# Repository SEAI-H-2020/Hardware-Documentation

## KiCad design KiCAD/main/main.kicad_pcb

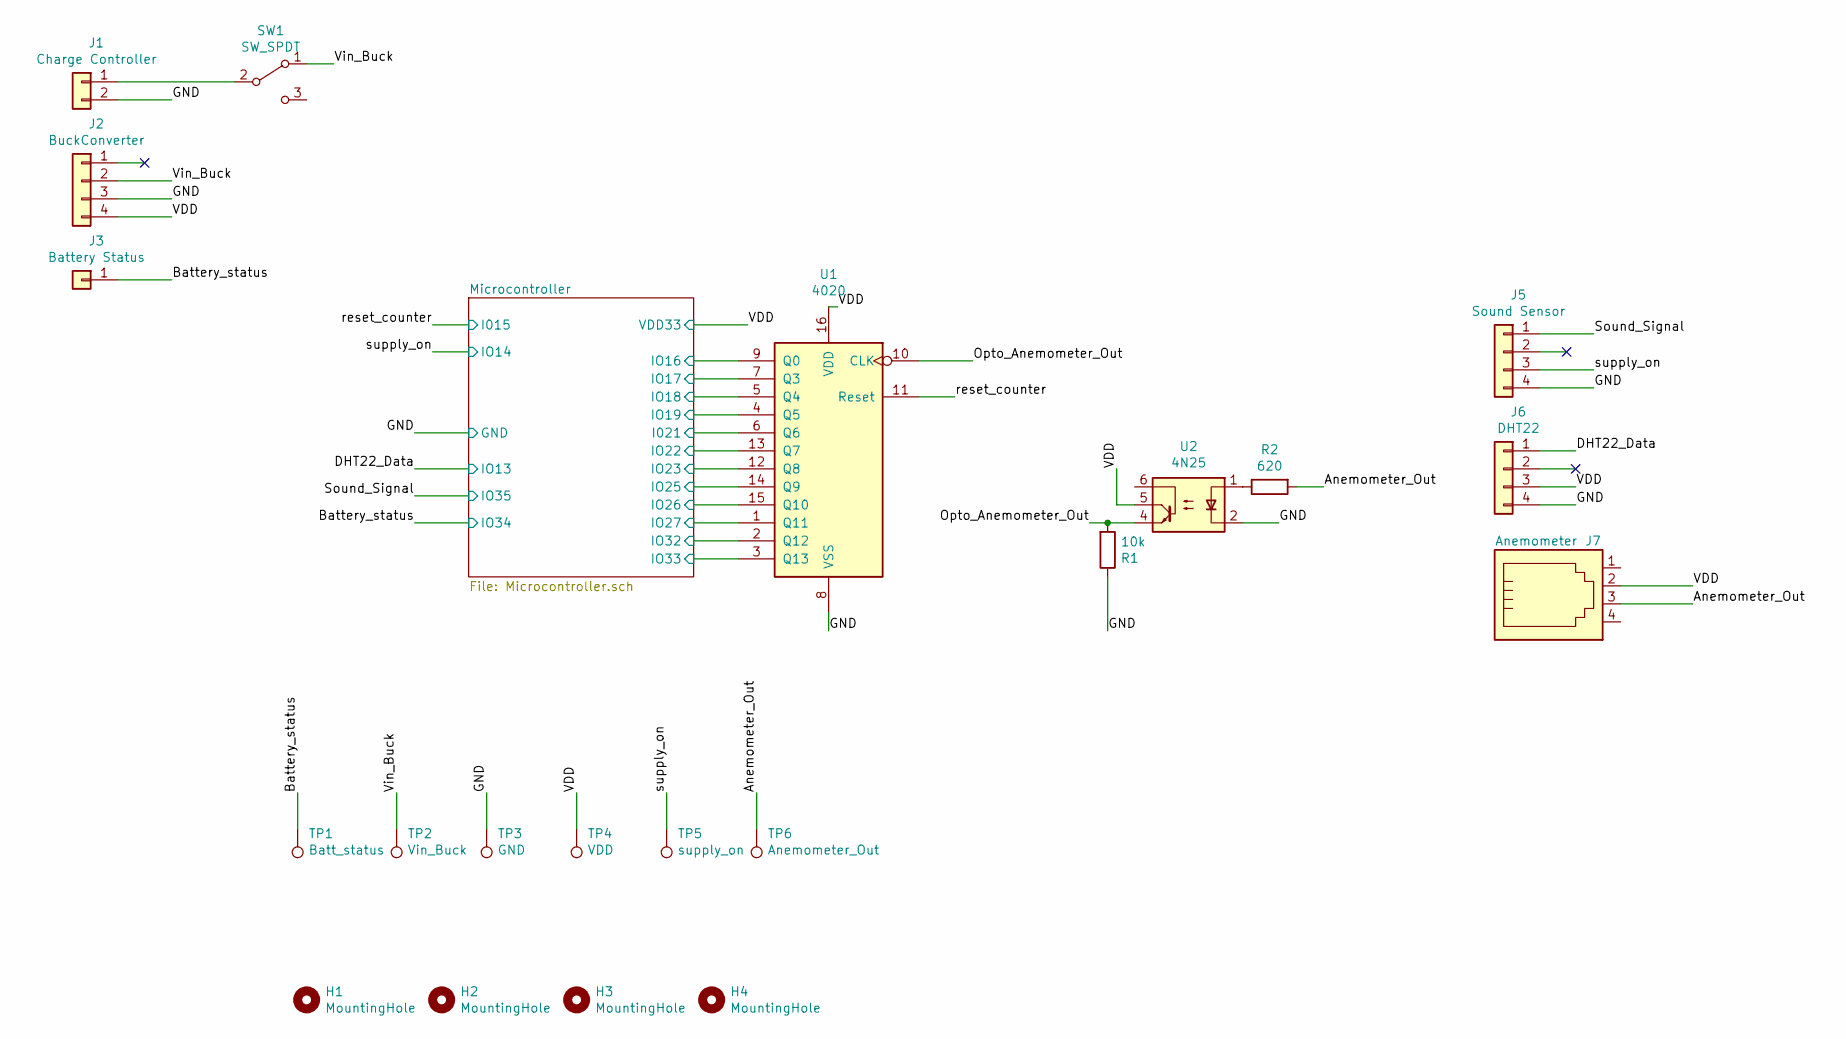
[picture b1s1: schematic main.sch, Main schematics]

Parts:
H1, H2, H3, H4: MountingHole; MountingHole_3.2mm_M3_Pad
J1: Charge Controller; JST_PH_B2B-PH-K_1x02_P2.00mm_Vertical
J2: BuckConverter; PinSocket_1x04_P2.54mm_Vertical
J3: Battery Status; PinHeader_1x01_P2.54mm_Vertical
J5: Sound Sensor; NS-Tech_Grove_1x04_P2mm_Vertical
J6: DHT22; NS-Tech_Grove_1x04_P2mm_Vertical
J7: Anemometer; RJ14_Connfly_DS1133-S4_Horizontal
R1: 10k; R_Axial_DIN0207_L6.3mm_D2.5mm_P10.16mm_Horizontal
R2: 620; R_Axial_DIN0207_L6.3mm_D2.5mm_P10.16mm_Horizontal
SW1: SW_SPDT; SW_CuK_JS202011AQN_DPDT_Angled
TP1: Batt_status; TestPoint_Pad_1.0x1.0mm
TP2: Vin_Buck; TestPoint_Pad_1.0x1.0mm
TP3: GND; TestPoint_Pad_1.0x1.0mm
TP4: VDD; TestPoint_Pad_1.0x1.0mm
TP5: supply_on; TestPoint_Pad_1.0x1.0mm
TP6: Anemometer_Out; TestPoint_Pad_1.0x1.0mm
U1: 4020; DIP-16_W7.62mm_LongPads
U2: 4N25; DIP-6_W7.62mm_LongPads

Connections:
+3V3: J2.4, J6.3, J7.2, TP4.1, U1.16 (VDD), U2.5; also elsewhere on the board
/Anemometer_Out: J7.3, R2.2, TP6.1
/Battery_status: J3.1, TP1.1; also elsewhere on the board
/DHT22_Data: J6.1; also elsewhere on the board
/Microcontroller/I021: U1.6 (Q6); also elsewhere on the board
/Microcontroller/IO16: U1.9 (Q0); also elsewhere on the board
/Microcontroller/IO17: U1.7 (Q3); also elsewhere on the board
/Microcontroller/IO18: U1.5 (Q4); also elsewhere on the board
/Microcontroller/IO19: U1.4 (Q5); also elsewhere on the board
/Microcontroller/IO22: U1.13 (Q7); also elsewhere on the board
/Microcontroller/IO23: U1.12 (Q8); also elsewhere on the board
/Microcontroller/IO25: U1.14 (Q9); also elsewhere on the board
/Microcontroller/IO26: U1.15 (Q10); also elsewhere on the board
/Microcontroller/IO27: U1.1 (Q11); also elsewhere on the board
/Microcontroller/IO32: U1.2 (Q12); also elsewhere on the board
/Microcontroller/IO33: U1.3 (Q13); also elsewhere on the board
/Opto_Anemometer_Out: R1.2, U1.10 (CLK), U2.4
/Sound_Signal: J5.1; also elsewhere on the board
/Vin_Buck: J2.2, SW1.1 (A), TP2.1
/reset_counter: U1.11 (Reset); also elsewhere on the board
/supply_on: J5.3, TP5.1; also elsewhere on the board
GND: J1.2, J2.3, J5.4, J6.4, R1.1, TP3.1, U1.8 (VSS), U2.2; also elsewhere on the board
unnamed: J1.1, SW1.2 (B)
unnamed: R2.1, U2.1

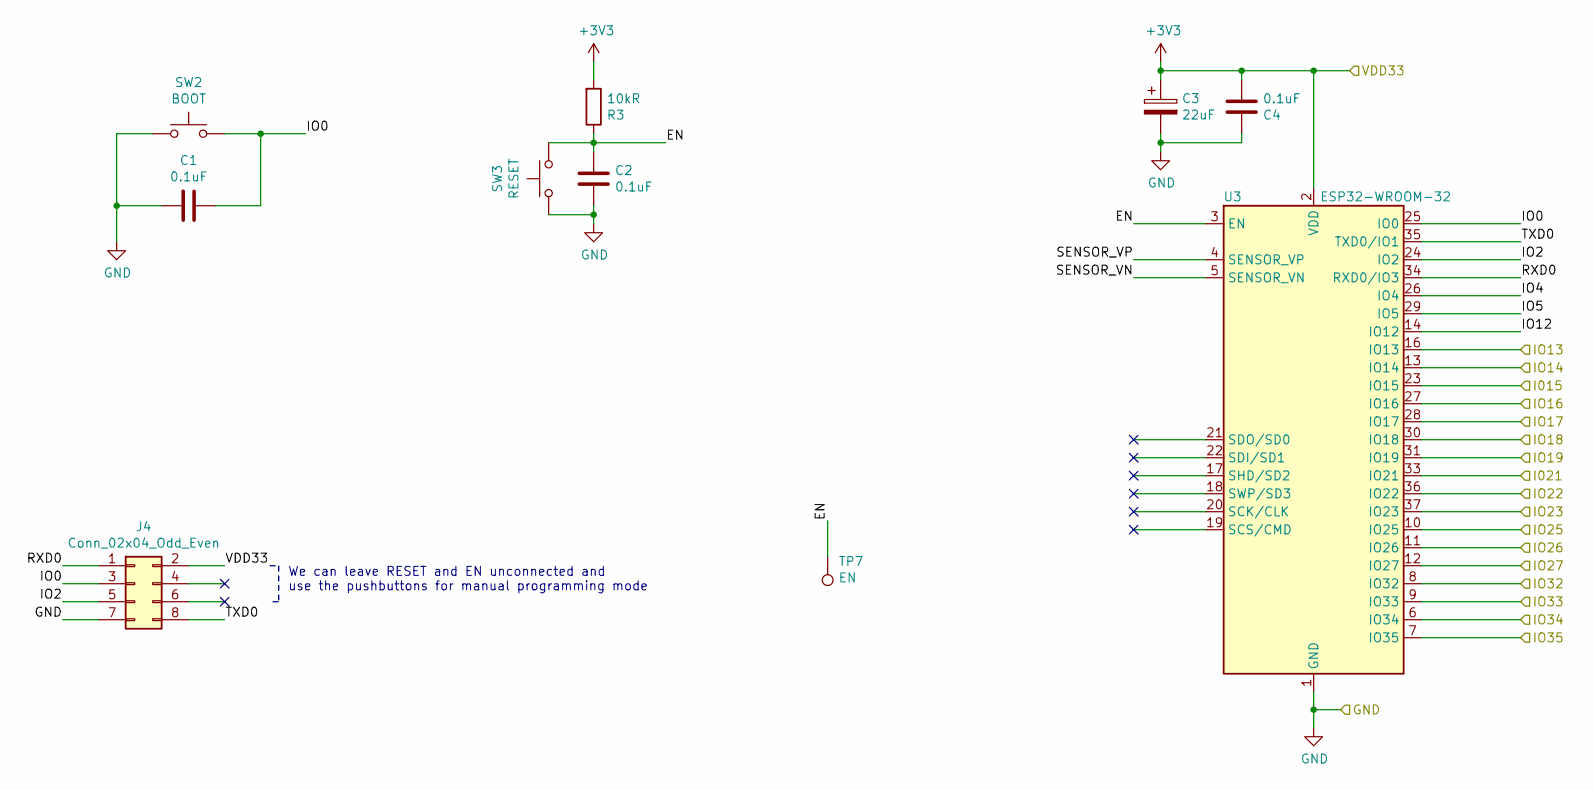
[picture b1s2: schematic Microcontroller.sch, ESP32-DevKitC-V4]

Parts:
C1, C4: 0.1uF; C_Disc_D4.3mm_W1.9mm_P5.00mm; Voltage 50V
C2: 0.1uF; C_Disc_D4.3mm_W1.9mm_P5.00mm; Voltage 50V; Tolerance 10%
C3: 22uF; CP_Radial_D6.3mm_P2.50mm; Voltage 10V
J4: Conn_02x04_Odd_Even; PinHeader_2x04_P2.54mm_Vertical
R3: 10kR; R_Axial_DIN0207_L6.3mm_D2.5mm_P10.16mm_Horizontal
SW2: BOOT; SW_PUSH_6mm
SW3: RESET; SW_PUSH_6mm
TP7: EN; TestPoint_Pad_1.0x1.0mm
U3: ESP32-WROOM-32

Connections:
+3V3: C3.1, C4.2, J4.2, R3.2, U3.2 (VDD); also elsewhere on the board
/Battery_status: U3.6 (IO34); also elsewhere on the board
/DHT22_Data: U3.16 (IO13); also elsewhere on the board
/Microcontroller/EN: C2.1, R3.1, SW3.2, TP7.1, U3.3 (EN)
/Microcontroller/I021: U3.33 (IO21); also elsewhere on the board
/Microcontroller/IO0: C1.2, J4.3, SW2.2, U3.25 (IO0)
/Microcontroller/IO2: J4.5, U3.24 (IO2)
/Microcontroller/IO4: U3.26 (IO4)
/Microcontroller/IO5: U3.29 (IO5)
/Microcontroller/IO12: U3.14 (IO12)
/Microcontroller/IO16: U3.27 (IO16); also elsewhere on the board
/Microcontroller/IO17: U3.28 (IO17); also elsewhere on the board
/Microcontroller/IO18: U3.30 (IO18); also elsewhere on the board
/Microcontroller/IO19: U3.31 (IO19); also elsewhere on the board
/Microcontroller/IO22: U3.36 (IO22); also elsewhere on the board
/Microcontroller/IO23: U3.37 (IO23); also elsewhere on the board
/Microcontroller/IO25: U3.10 (IO25); also elsewhere on the board
/Microcontroller/IO26: U3.11 (IO26); also elsewhere on the board
/Microcontroller/IO27: U3.12 (IO27); also elsewhere on the board
/Microcontroller/IO32: U3.8 (IO32); also elsewhere on the board
/Microcontroller/IO33: U3.9 (IO33); also elsewhere on the board
/Microcontroller/RXD0: J4.1, U3.34 (RXD0/IO3)
/Microcontroller/SENSOR_VN: U3.5 (SENSOR_VN)
/Microcontroller/SENSOR_VP: U3.4 (SENSOR_VP)
/Microcontroller/TXD0: J4.8, U3.35 (TXD0/IO1)
/Sound_Signal: U3.7 (IO35); also elsewhere on the board
/reset_counter: U3.23 (IO15); also elsewhere on the board
/supply_on: U3.13 (IO14); also elsewhere on the board
GND: C1.1, C2.2, C3.2, C4.1, J4.7, SW2.1, SW3.1, U3.1 (GND), U3.15 (GND), U3.38 (GND), U3.39 (GND); also elsewhere on the board

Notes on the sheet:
We can leave RESET and EN unconnected and use the pushbuttons for manual programming mode

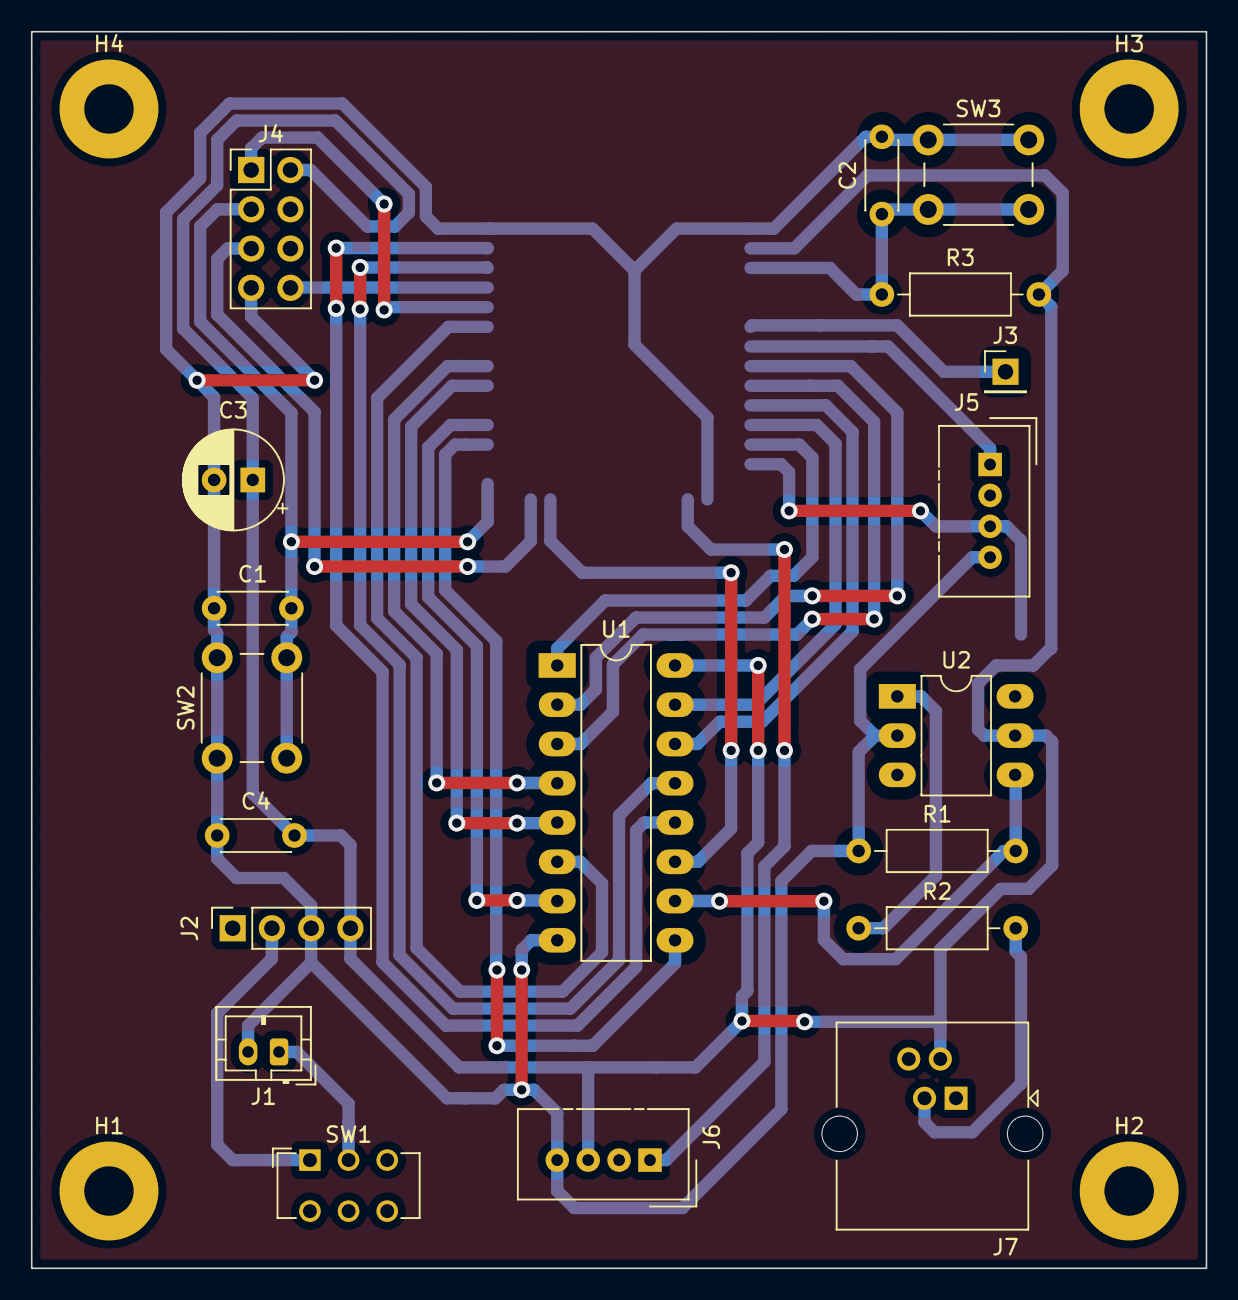
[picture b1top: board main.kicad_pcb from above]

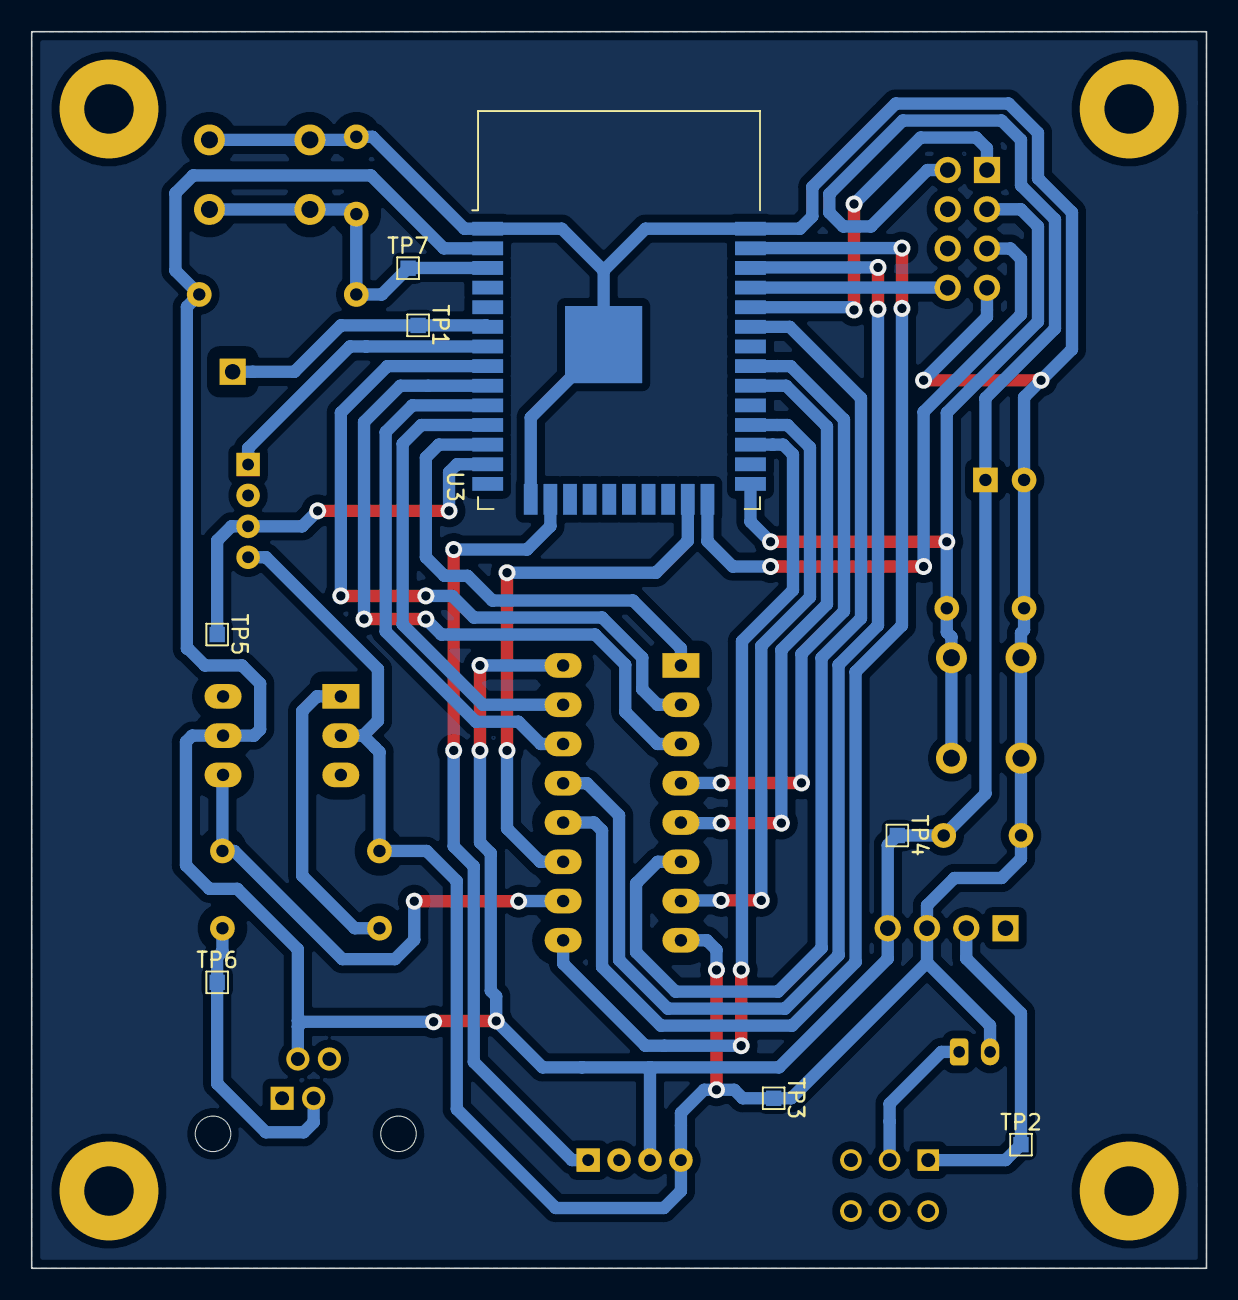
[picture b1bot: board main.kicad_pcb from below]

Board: 2 copper layers, 76.0 x 80.0 mm, 31 parts (8 on the bottom side), 29 nets.

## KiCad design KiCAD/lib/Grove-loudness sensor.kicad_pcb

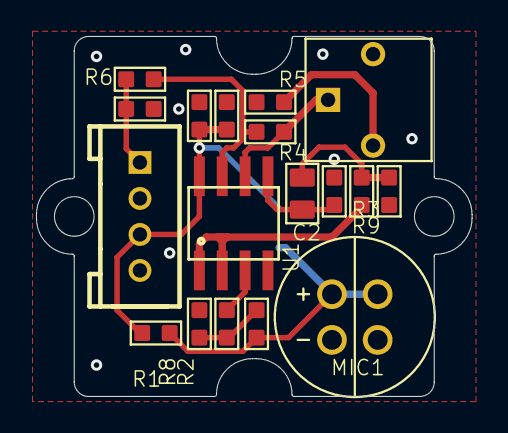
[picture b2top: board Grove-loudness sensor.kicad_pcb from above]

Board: 2 copper layers, 24.2 x 20.0 mm, 23 parts (0 on the bottom side), 12 nets.

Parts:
C1, C3, C5: 1uF; C0603
C2: 4.7uF; C0805
C4: 100nF; C0603
C6: 4.7pF; C0603
J2: TWIG_2.0; 2.0_1X4
MIC1, MIC2: microphone; 2P-D8.9MM
R1: 10k; R0603
R2, R8: 100k; R0603
R3: 16K; R0603
R4: 560k; R0603
R5: 1K; R0603
R6: 47K; R0603
R7: 1k; 3P-SQUA-7X6.8
R9: 10K; R0603
U1: LM2904DR; SO08
U4: SENSOR-MULPS4CX; 4P-SMD-2.95X3.76X1.1H
U$1: OSHW_FILLX150_NOTEXT
U$2: 1U-DIM-W_-DRILL
U$3: TWIGLOGO

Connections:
/MIC: C1.1, MIC1.1, MIC2.1, R1.1, U4.1
/SIG: C3.1, J2.1, R6.2
/VCC: C4.1, C5.2, J2.3, R1.2, U4.4
GND: C3.2, C4.2, C5.1, C6.1, J2.4, MIC1.2, MIC2.2, R3.1, R5.1, R8.1, U1.4, U4.2, U4.3
unnamed: C1.2, R2.1, R8.2
unnamed: C2.1, R3.2, U1.5
unnamed: C2.2, C6.2, R9.2
unnamed: R2.2, U1.3
unnamed: R4.1, R7.3, U1.6
unnamed: R4.2, R6.1, U1.7
unnamed: R5.2, R7.1
unnamed: R9.1, U1.1, U1.2

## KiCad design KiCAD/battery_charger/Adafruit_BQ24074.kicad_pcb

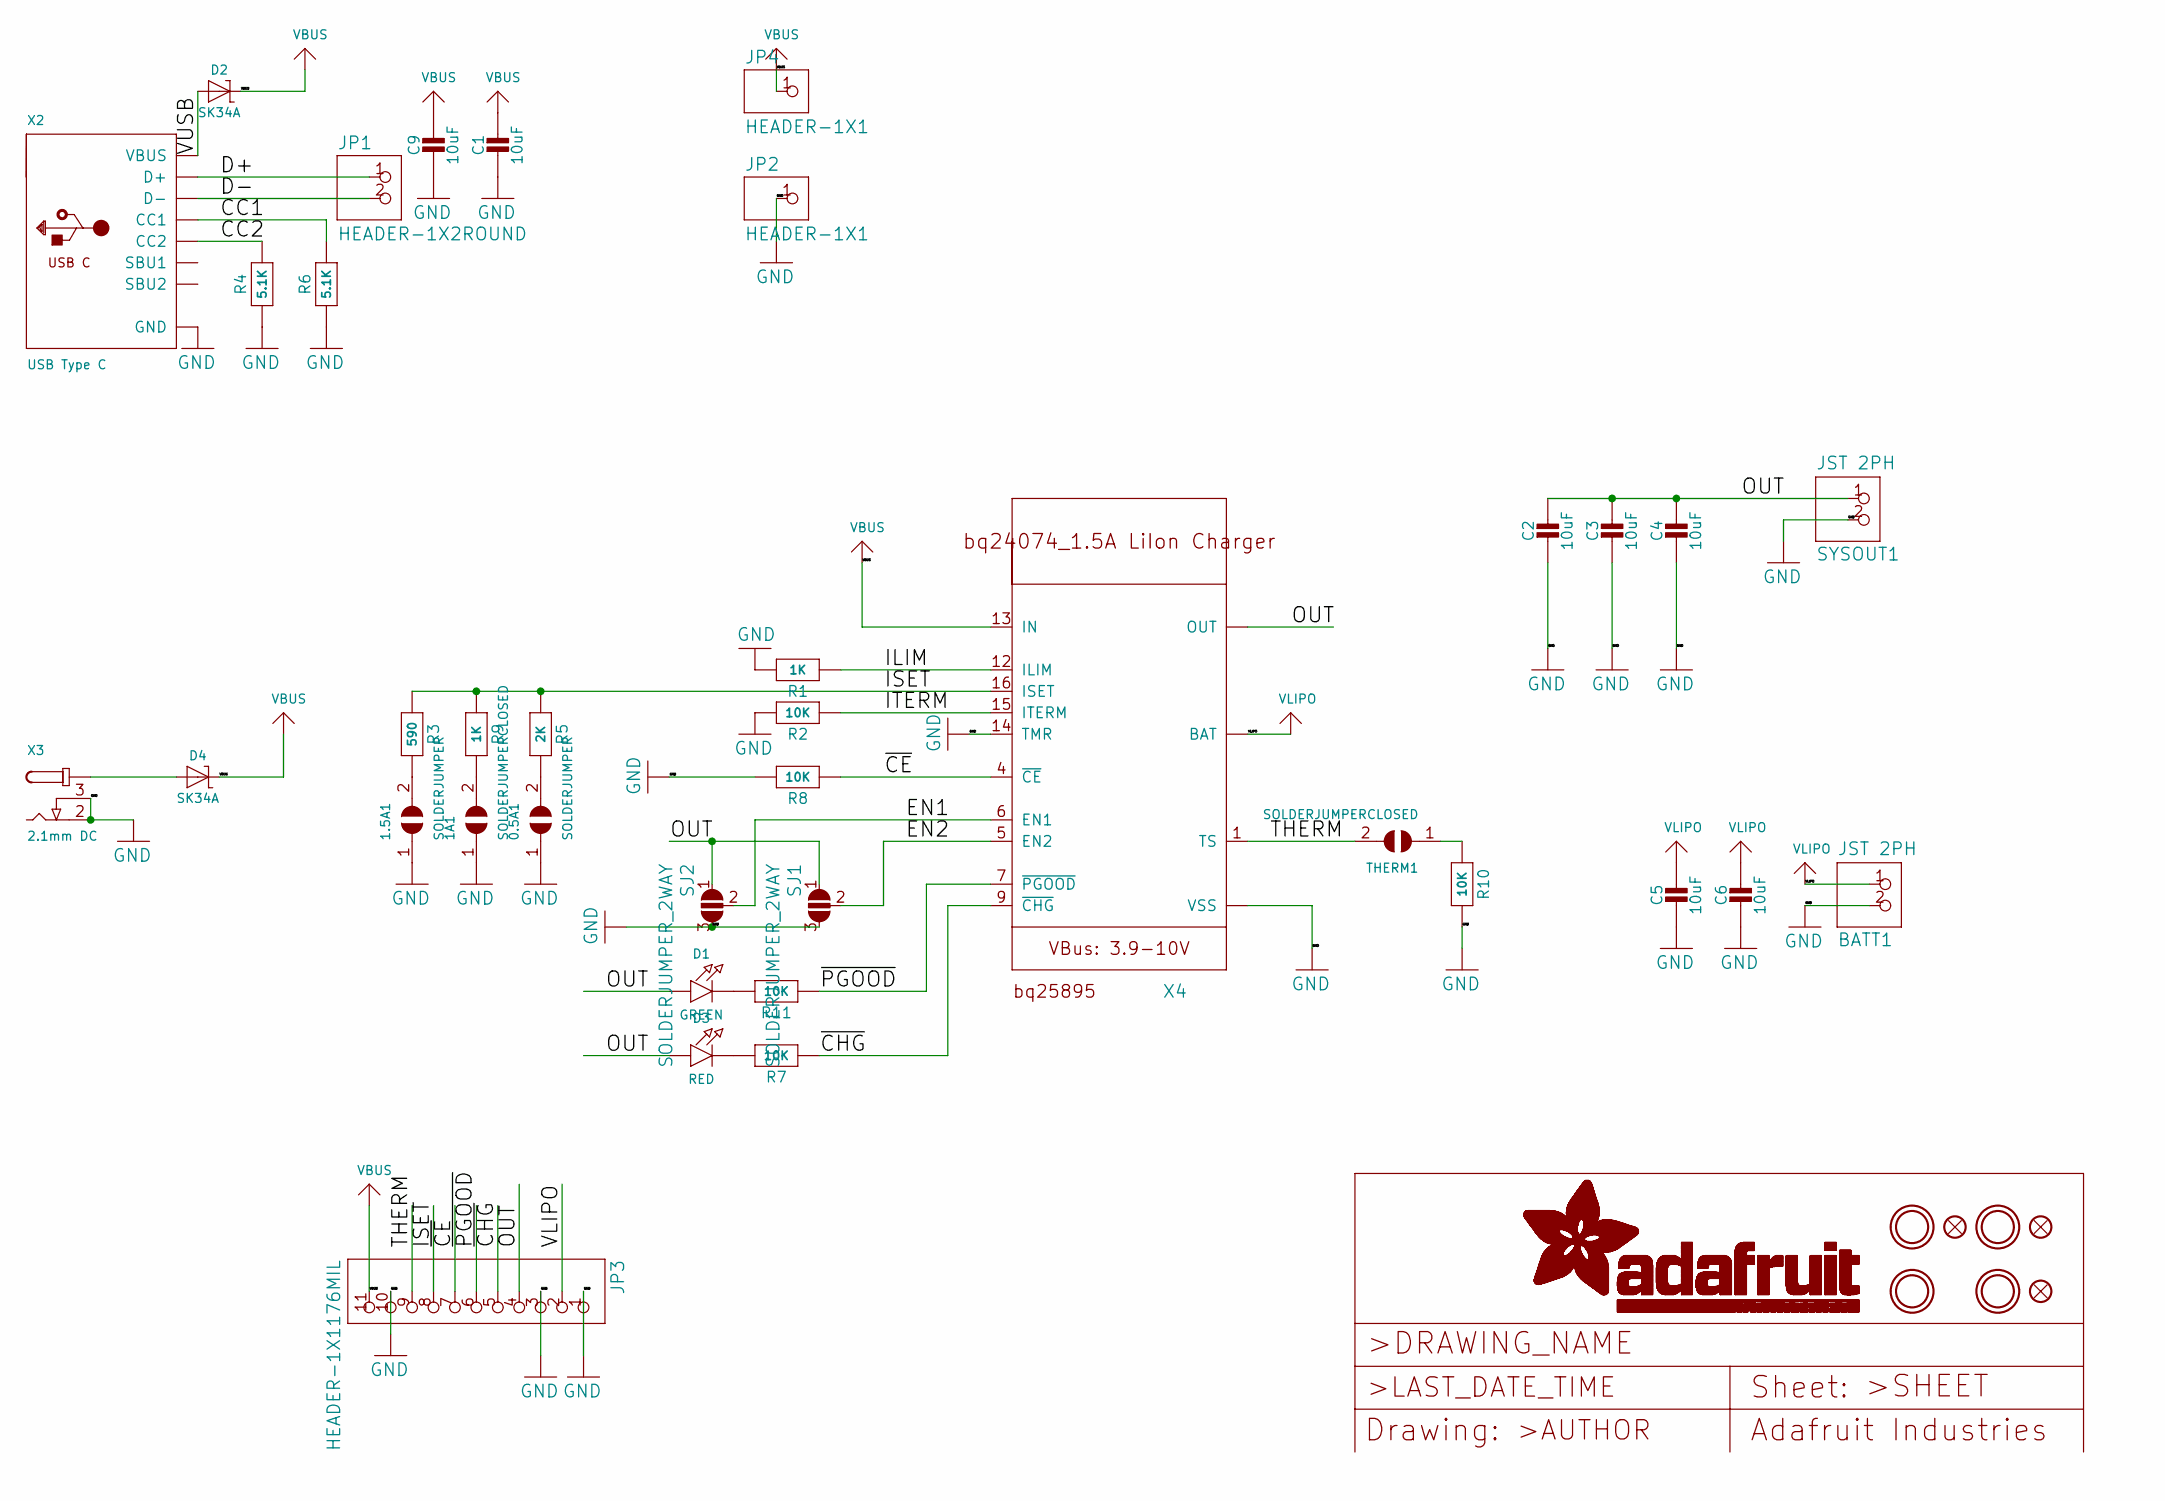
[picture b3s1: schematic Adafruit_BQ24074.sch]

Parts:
0.5A1, 1.5A1: SOLDERJUMPER; SOLDERJUMPER_ARROW_NOPASTE
1A1: SOLDERJUMPERCLOSED; SOLDERJUMPER_CLOSEDWIRE
BATT1: JST 2PH; JST-PH-2-SMT-RA
C1, C2, C3, C4, C5, C6, C9: 10uF; 0805-NO
D1: GREEN; CHIPLED_0603
D2, D4: SK34A; SMADIODE
D3: RED; CHIPLED_0603
FID1, FID2, FID3: FIDUCIAL_1MM
JP1: HEADER-1X2ROUND; 1X02_ROUND
JP2, JP4: HEADER-1X1; 1X01_OVAL
JP3: HEADER-1X1176MIL; 1X11_ROUND_76
R1, R9: 1K; 0603-NO
R2, R7, R8, R10, R11: 10K; 0603-NO
R3: 590; 0603-NO
R4, R6: 5.1K; 0603-NO
R5: 2K; 0603-NO
SJ1, SJ2: SOLDERJUMPER_2WAY; SOLDERJUMPER_2WAY_OPEN_NOPASTE
SYSOUT1: JST 2PH; JST-PH-2-SMT-RA
THERM1: SOLDERJUMPERCLOSED; SOLDERJUMPER_CLOSEDWIRE
U$3, U$4, U$11, U$12: MOUNTINGHOLE2.5; MOUNTINGHOLE_2.5_PLATED
X2: USB Type C; USB_C_CUSB31-CFM2AX-01-X
X3: 2.1mm DC; DCJACK_2MM_SMT
X4: BQ24074; QFN16_3MM

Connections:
/CC1: R6.2, X2.A5 (CC1)
/CC2: R4.2, X2.B5 (CC2)
/D+: JP1.1, X2.A6 (D+), X2.B6 (D+)
/D-: JP1.2, X2.A7 (D-), X2.B7 (D-)
/EN1: SJ2.2, X4.6 (EN1)
/EN2: SJ1.2, X4.5 (EN2)
/ILIM: R1.1, X4.12 (ILIM)
/ISET: JP3.8, R3.1, R5.1, R9.1, X4.16 (ISET)
/ITERM: R2.1, X4.15 (ITERM)
/OUT: C2.1, C3.1, C4.1, D1.A, D3.A, JP3.4, SJ1.1, SJ2.1, SYSOUT1.1 (2), X4.10 (OUT), X4.11 (OUT)
/THERM: JP3.9, THERM1.2, X4.1 (TS)
/VUSB: D2.A, X2.A4B9 (VBUS), X2.B4A9 (VBUS)
/~CE: JP3.7, R8.1, X4.4 (~CE)
/~CHG: JP3.5, R7.1, X4.9 (~CHG)
/~PGOOD: JP3.6, R11.1, X4.7 (~PGOOD)
GND: 0.5A1.1, 1.5A1.1, 1A1.1, BATT1.2 (1), C1.2, C2.2, C3.2, C4.2, C5.2, C6.2, C9.2, JP2.1, JP3.1, JP3.3, JP3.10, R1.2, R2.2, R4.1, R6.1, R8.2, R10.2, SJ1.3, SJ2.3, SYSOUT1.2 (1), X2.A1B12 (GND), X2.B1A12 (GND), X3.2 (GND), X3.3 (GNDBREAK), X4.8 (VSS), X4.14 (TMR), X4.THERMAL (VSS)
unnamed: 0.5A1.2, R5.2
unnamed: 1.5A1.2, R3.2
unnamed: 1A1.2, R9.2
unnamed: D1.C, R11.2
unnamed: D3.C, R7.2
unnamed: D4.A, X3.1 (PWR), X3.1' (PWR)
unnamed: R10.1, THERM1.1
VBUS: C1.1, C9.1, D2.C, D4.C, JP3.11, JP4.1, X4.13 (IN)
VLIPO: BATT1.1 (2), C5.1, C6.1, JP3.2, X4.2 (BAT), X4.3 (BAT)

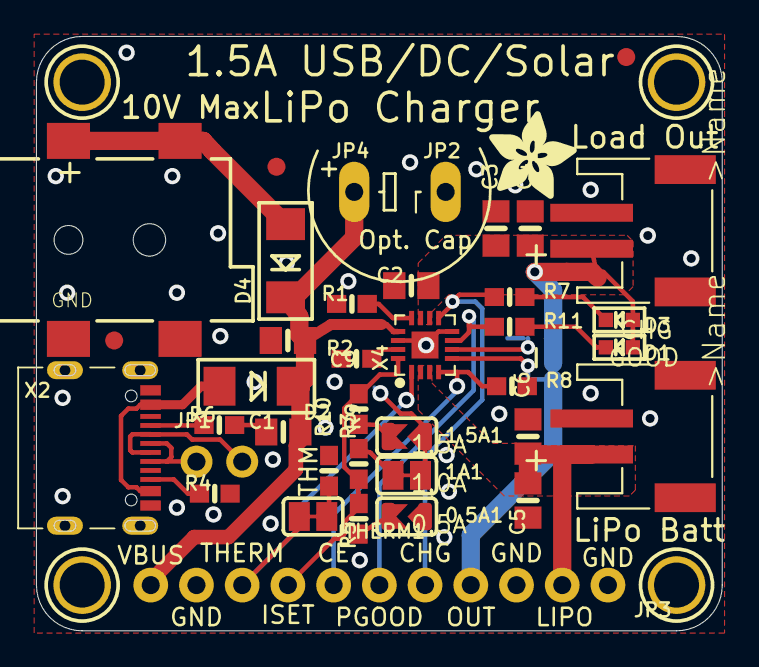
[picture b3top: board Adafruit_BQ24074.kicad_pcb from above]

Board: 2 copper layers, 38.1 x 33.0 mm, 46 parts (0 on the bottom side), 25 nets.

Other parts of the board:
U$14: ADAFRUIT_5MM
U$18: PCBFEAT-REV-040

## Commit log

2020-10-22 Prepare KiCAD folder
2020-10-22 Prepare /doc folder.
2020-10-22 Add ESP32-WROOM-32 datasheet.
2020-10-22 Add clean KiCAD project for the prototyping schematics
2020-10-22 Add ESP32 hardware design guidelines to documentation
2020-10-22 Add ESP32-WROOM-32 hardware reference link
2020-10-22 Add ESP32-WROOM-32 power and enable connections
2020-10-22 Add ESP32 DevKitC V4 hardware reference link
2020-10-23 Cleanup schematic to start transcribing the ESP32-DevKitC-V4 schematics
2020-10-23 Add devkit's power supply and esp32 module schematics
2020-10-23 Add switch button connections
2020-10-23 Finish labels on ESP32 module
2020-10-23 Add connector connections
2020-10-23 Add initial USB connections and circuits
2020-10-23 esquemático do sensor de som
2020-10-23 Add files via upload
    esquemático do sensor de som
2020-11-01 Move ESP32 docs to /doc/ESP32
2020-11-01 Add 3V3 regulator documents
2020-11-08 esquemático do sensor de som e circuito de carregamento
2020-11-11 esquemático do buck-converter
2020-11-13 Add DHT22 as project library
2020-11-13 Move battery charger library into /KiCAD/lib
2020-11-13 Move sound sensor library to /KiCAD/lib
2020-11-13 Move buck converter library to /KiCAD/lib
2020-11-13 Move buck converter documentation to /doc/buck_converter
2020-11-13 Add battery charger as project library
2020-11-13 Fix local project footprint library name to LOCAL
2020-11-13 Add buck converter as project library
2020-11-13 Add sound sensor as project library
2020-11-13 Change local labels to hierarchical labels
2020-11-13 Export all signals to the schematic reference
2020-11-13 Ignore backup files
2020-11-13 Fix backup file ignore rule
2020-11-13 Add missing connections on ESP32-DevKitC-V4
2020-11-13 Make library paths relative and disable manually created schematics of sensors as libraries
2020-11-13 Add ESP32-DevKitC-V4 reference schematic to docs
2020-11-13 Sound Sensor eagle schematic
2020-11-15 Adicionadas as ligações entre componentes
    Necessário verificar quais sheets não estão a ser utilizadas e eliminar
2020-11-19 Correction of miss placed folder
2020-11-19 Revert "Merge branch 'devel' into luis"
    This reverts commit 12b203dde500fe9434468d0bdc425e41ba632681, reversing
    changes made to 5ff5ea5b06c891ff9ca50429f18fec54b7dc7daa.
2020-11-19 Add missing DHT22 library path on project config
2020-11-19 Improve gitignore
2020-11-19 Remove ignored backup files
2020-11-19 Remove unneeded project files
    These were used to create the schematics of diferent modules that were already included in the 'prototype.pro' project, so they're no longer needed
2020-11-19 Remove duplicate DHT22 library
    This library is already present in /KiCAD/lib/
2020-11-19 Remove duplicate Soud_sensor schematic
2020-11-19 Remove duplicate buck_converter schematic
2020-11-19 Remove duplicate Grove-loudness sensor files
2020-11-19 Fix project reference to the grove-soudness sensor 'library'
2020-11-19 Remove duplicate power supply schematics
2020-11-19 Create copy of ESP32-DevKitC-V4 in lib
2020-11-19 Improve Anemometer schematics
2020-11-19 Update files after changes (misc)
2020-11-19 Improve looks (minor)
2020-11-19 Add main schematic for final design
2020-11-25 Import prototype schematics to start final schematics
2020-11-25 Move ESP32-DevKitC-V4 to Microcontroller
    and remove unneeded/unused stuff included in the development kit
2020-11-25 Remove test label
2020-11-25 Add missing EN label
2020-11-25 Improve BuckConverter schematic readability
2020-11-25 Fix unconnected line
2020-11-25 Revert "Merge pull request #70 from SEAI-H-2020/simao"
    This reverts commit 8f7a5ddb988a44fc582282c64fd26dad6a2def48, reversing
    changes made to a29114cc5d56bd4d0684a9d09dd32e41573018a7.
2020-11-25 Add missing local project footprint reference
2020-11-25 Remove unneded header
2020-11-27 Include missing VDD33 label on the microcontroller schematics
2020-11-27 Add missing GND label on the microcontroller
    and move unneded signals and signals that should not be normally accessible as NC pins
2020-11-27 Unexport unneded signals from the microcontroller sheet
2020-11-27 Add programming header for the microcontroller
2020-11-27 Rename EN button to RESET
    and add comment about the ENABLE and RESET signals from the programming header
2020-11-27 Assign footprints to components on the microcontroller sheet
2020-11-27 Improve readability on main schematic
2020-11-27 Replace sound sensor and buck converter with the respective connectors
2020-11-27 Add simple pcb design
    still buggy
2020-11-29 Better track size and all connections done on preliminary pcb
2020-11-29 Add example images for the PCB
2020-12-02 alimentação e proteção
2020-12-03 algumas correções
2020-12-06 alimentação através do micro
2020-12-06 troca do DPDT por um SPDT
2020-12-06 Modelo 3d da caixa
    Protótipo do modelo para impressão da caixa
2020-12-06 Corrigir commit
2020-12-06 Modelo 3d da Box
    Modelo do protótipo da box para teste
    Pdf do esquematico do modelo
2020-12-07 Fix footprints
2020-12-07 Clear anotations
2020-12-07 Reanotate everything and assign missing footprints
2020-12-07 Fix library reference (again)
2020-12-07 Improve EN circuit for microcontroller
2020-12-07 Fix battery charger connectors
2020-12-07 Preliminary layout with fixed component pins
2020-12-07 All connections done
2020-12-07 Add unconnected GND
2020-12-07 Preliminary final PCB
2020-12-07 Reorganize PCB previews
2020-12-07 Adjust tracks for 0.8mm width and 0.35mm clearance
2020-12-08 Extend PCB limits and add M3 mounting holes
2020-12-08 Update do modelo
    Adição do suporte da pcb e reornagização dos compoenentes.
    Adiçao do modelo da bateria
2020-12-08 Fix pcb width
2020-12-08 Fix layout measurements
2020-12-08 Add production files
2020-12-08 Move production files to corresponding folders
2020-12-17 Adjust via size and decrease clearance to 0.3mm
2020-12-17 Change ON switch footprint
2020-12-17 Export footprint associations
2020-12-17 Add production v1.1 overview images
2020-12-17 Update fp-info-cache
2020-12-18 Add some pcb test points
2020-12-29 Replace all possible footprints to THT variants
    Also clear current PCB design and update component footprints
2020-12-29 Expand design vertically, reposition components and re-track
2020-12-29 Add overview images
2020-12-29 Changes KiCAD saved after exporting images
    I dont't really know what changed, but works fine.
2021-01-03 increase via pad to 1.1mm and allow space for fixtures
2021-01-04 Replace DHT22 and cound sensor JST connector with GROVE connectors
    Also replace mounting holes and add them to the reference schematic
2021-01-04 Increase margins for the fixtures
2021-01-04 Re-annotate connectors
2021-01-04 Improve placement of the Power switch, RJ14, J3 and J5 connectors
2021-01-04 Update metadata and cmp/netlist/bom files
2021-01-04 Add PDF schematics
2021-01-04 Move PCB exports to documentation
2021-01-04 Move miscelaneous exports to /doc
2021-01-04 Move schematic into versioned folder
2021-01-08 Change DHT22 supply to VDD
2021-01-08 Update frame version info and export v2.3 production files
2021-01-08 Give more clearances
    - Increased clearance between the power switch and the board edge (adjusting J1 and J2 as necessary)
    - increased clearance from tracks to the H4 pad
2021-01-08 Refill empty zones (missing in last commit)
2021-01-08 Fix placement marker for SW1
2021-01-08 Beggining of the clearances improvement
2021-01-08 Finish clearances improvement
2021-01-09 Refill empty zones (again missing from previous commit)
2021-01-10 Improve some more clearances
    As requested in https://github.com/SEAI-H-2020/Hardware-Documentation/pull/114#issuecomment-757465732
2021-01-11 Update version information
2021-01-11 Export v2.3.1 docs
2021-01-17 Fotos e ficheiro
    Adicionadas fotos do modelo da box e ficheiro do fusion
    Versao ja otimizada pós 1a impressao
2021-01-17 Adicionados desenhos
    Desenhos da box e suporte
2021-01-18 Add more 3D previews of the PCB
2021-01-21 Criticas Anibal
2021-01-21 ATA critics
2021-01-21 Criticas do Tasso
